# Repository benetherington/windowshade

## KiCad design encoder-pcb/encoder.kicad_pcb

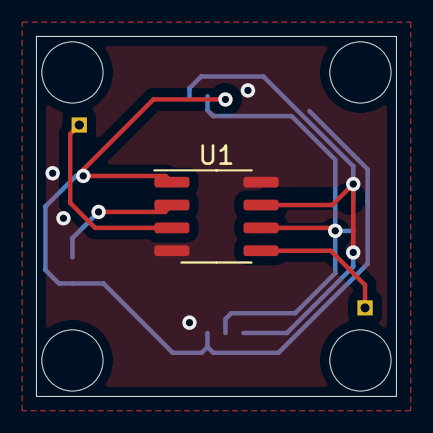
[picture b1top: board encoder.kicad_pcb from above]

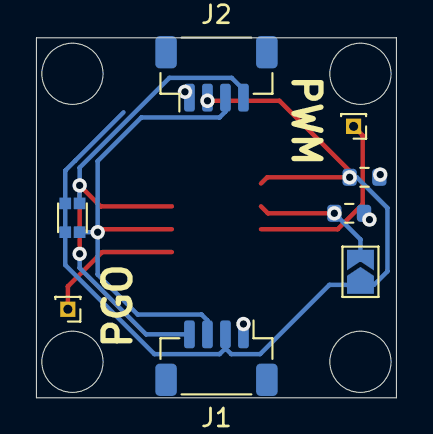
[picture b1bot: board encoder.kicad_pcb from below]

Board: 2 copper layers, 20.0 x 20.0 mm, 9 parts (8 on the bottom side), 7 nets.

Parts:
C2: 0.1uF; R_0603_1608Metric
C3: ~10uF; R_0603_1608Metric
J1, J2: Conn_01x04; JST_SH_BM04B-SRSS-TB_1x04-1MP_P1.00mm_Vertical
JP1: ~3v3; SolderJumper-2_P1.3mm_Open_TrianglePad1.0x1.5mm
R1-R2: EXB34V
TP1: PWM; PinHeader_1x01_P1.00mm_Vertical
TP2: PROGRAM; PinHeader_1x01_P1.00mm_Vertical
U1: AS5600; SOIC-8_3.9x4.9mm_P1.27mm

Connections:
/3V3: C3.1, JP1.2, U1.2
GND: C2.1, C3.2, J1.1, J2.1, U1.4, U1.8
PGO: TP2.1, U1.5
PWM: TP1.1, U1.3
SCL: J1.4, J2.4, R1-R2.3, U1.7
SDA: J1.3, J2.3, R1-R2.1, U1.6
VCC: C2.2, J1.2, J2.2, JP1.1, R1-R2.2, R1-R2.4, U1.1

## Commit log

2022-07-11 whoops
2022-07-11 cad files
2022-07-11 RP2040 PIO tests
2022-07-11 Stepper motor test
2022-07-11 DC motor first code
2022-07-11 trapezoidal curve test
2022-07-11 update run on save script for black
2022-07-11 Ignore run on save
2022-07-12 Fix throttle calculator bug
2022-07-12 Update watchdog, reorganize
2022-07-12 update logger
2022-07-12 Update cir-py
2022-07-12 Stop a little short of target to prevent a watchdog violation
2022-07-12 Hard-code settle curve invalid point
2022-07-12 Fix sliding window throttle average, parametrize
2022-07-12 Fix major bug in watchdog that prevents ANY negative movement
2022-07-12 Store max error before raising exception
2022-07-12 Tweak exception message
2022-07-14 Add nvm use
2022-07-14 tidy
2022-07-14 Add comments
2022-07-14 Add circuitpython VS extension
